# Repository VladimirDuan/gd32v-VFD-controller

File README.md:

# gd32v-VFD-controller

## The HNV-12SS62 VFD screen:

## GD32V rv32imac microcontroller:

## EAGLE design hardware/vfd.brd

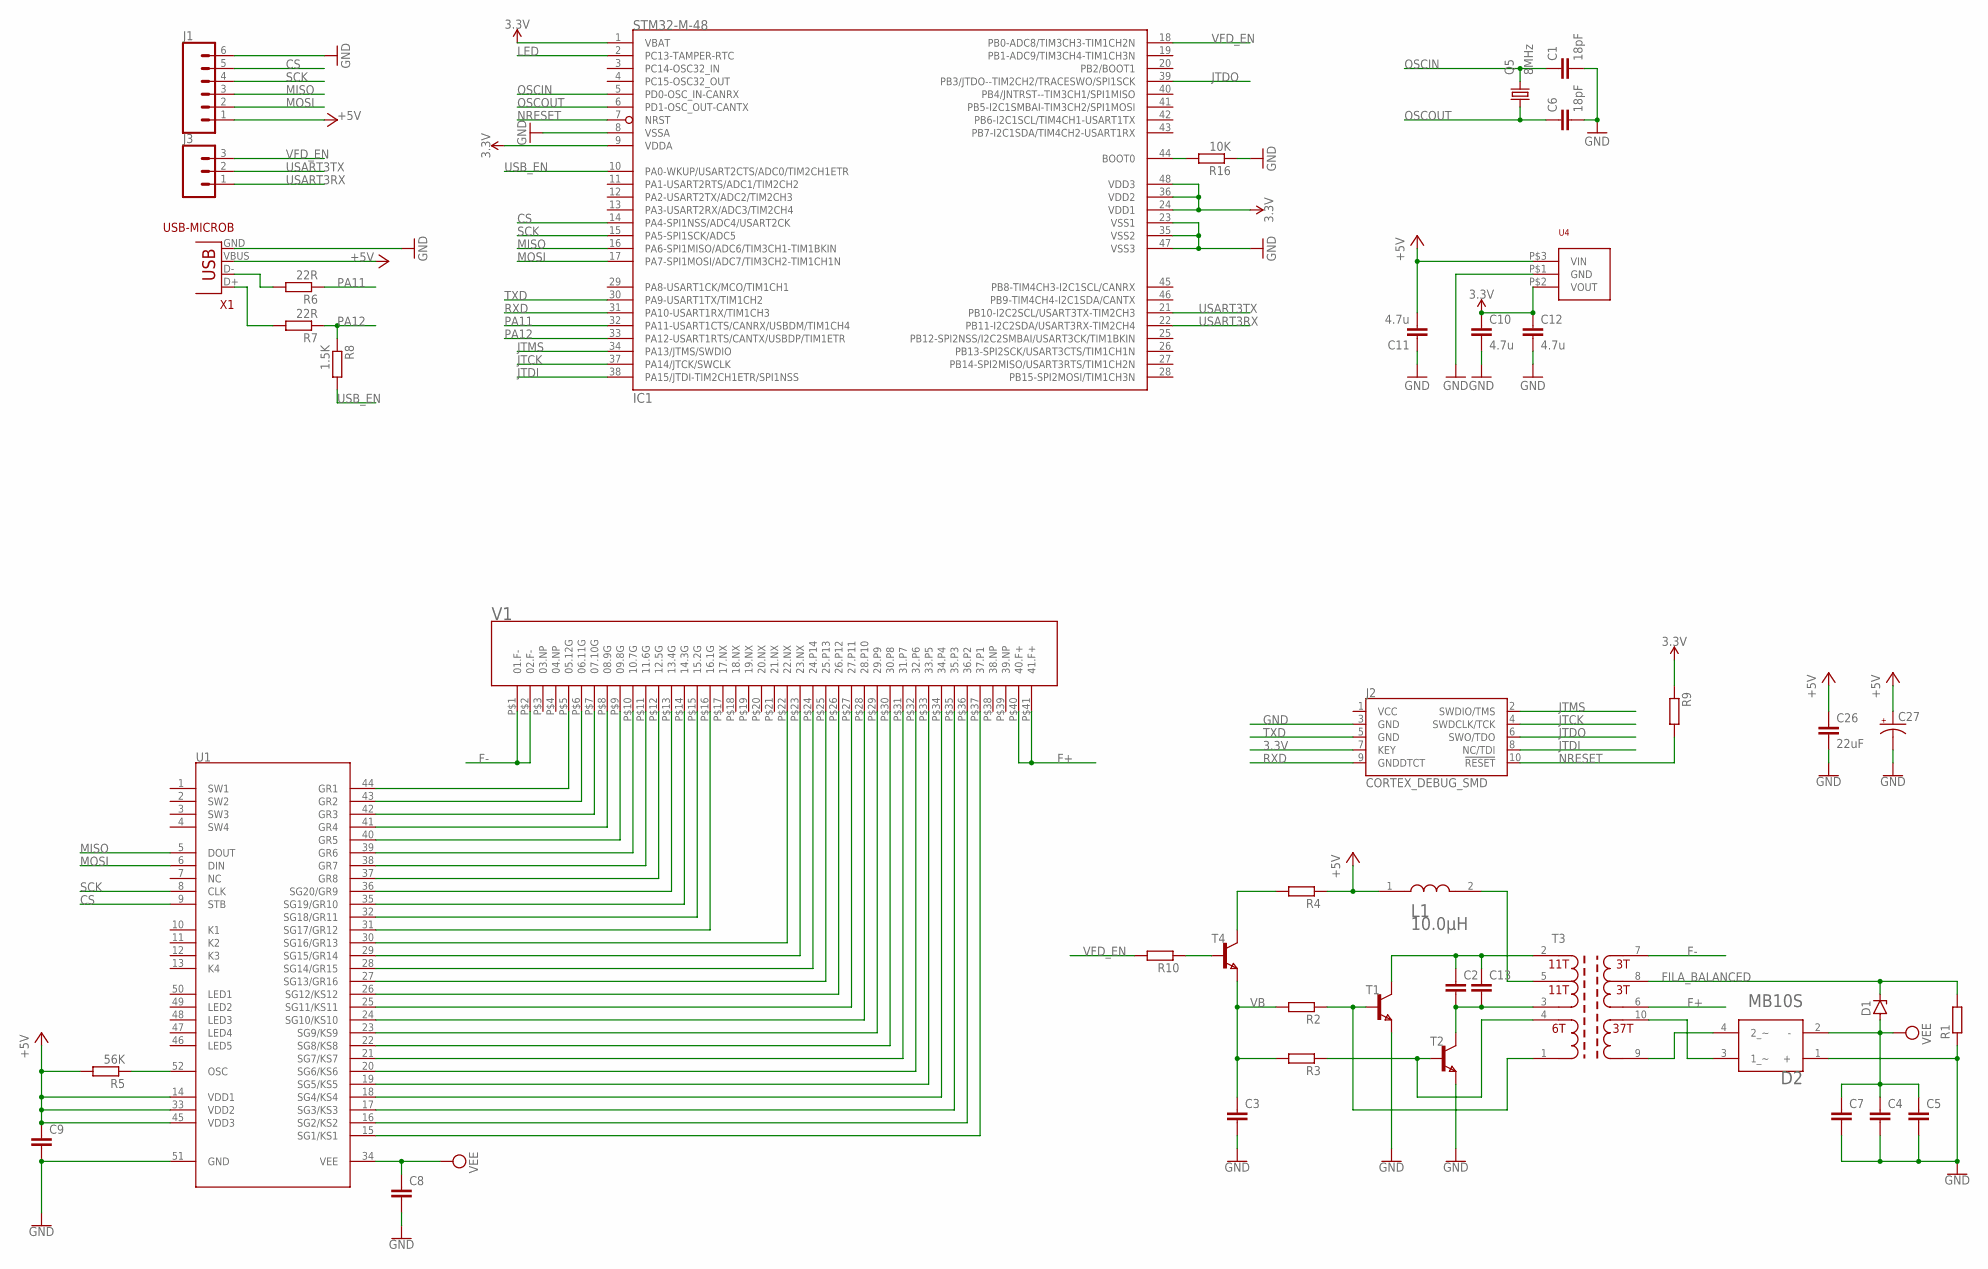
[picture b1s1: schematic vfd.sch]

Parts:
C1, C6: 18pF; C0603
C2, C13: C-EUC1206; C1206
C3, C4, C5, C7, C8, C9: C-EUC0805; C0805
C10, C11, C12: 4.7u; 0805
C26: 22uF; C1206
C27: CPOL-US153CLV-0807; 153CLV-0807
D1: ZENER-DIODESOD80C; SOD80C
D2: ON_SEMI_MB10SON_SEMI_MB10S_0_0; ON_SEMI_MB10S_0
IC1: STM32-M-48; LQFP48
J1: CONN_06NO_SILK_FEMALE_PTH; 1X06_NO_SILK
J2: CORTEX_DEBUG_SMD; SAMTECH_FTSH-105-01
J3: CONN_031X03_NO_SILK; 1X03_NO_SILK
L1: TDK_SLF7045T-100M1R3-PF; ASWPA8050
Q5: 8MHz; 3.2X2.5_KX-7
R1, R2, R3, R4, R9, R10: R-EU_R0603; R0603
R5: 56K; R0603
R6, R7: 22R; R0603
R8: 1.5K; R0603
R16: 10K; R0603
T1, T2, T4: NPNSOT23; SOT-23
T3: TRANS_VFD_ER10P5; ER10P5
U1: PT6311B; QFP52_SOT379-1
U4: MCP1703SOT-3.3V; SOT-23A
V1: VFD_12SS62; 12SS62
X1: USB-MICROB

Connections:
3.3V: C10.1, C12.1, IC1.1 (VBAT), IC1.9 (VDDA), IC1.24 (VDD1), IC1.36 (VDD2), IC1.48 (VDD3), J2.7 (KEY), R9.1, U4.P$2 (VOUT)
+5V: C9.1, C11.2, C26.1, C27.+, J1.1, L1.1, R4.1, R5.2, U1.14 (VDD1), U1.33 (VDD2), U1.45 (VDD3), U4.P$3 (VIN), X1.VBUS
CS: IC1.14 (PA4-SPI1NSS/ADC4/USART2CK), J1.5, U1.9 (STB)
F+: T3.6, V1.P$40 (40.F+), V1.P$41 (41.F+)
F-: T3.7, V1.P$1 (01.F-), V1.P$2 (02.F-)
FILA_BALANCED: D1.C, R1.2, T3.8
GND: C1.2, C3.2, C4.2, C5.2, C6.2, C7.2, C8.2, C9.2, C10.2, C11.1, C12.2, C26.2, C27.-, D2.1 (+), IC1.8 (VSSA), IC1.23 (VSS1), IC1.35 (VSS2), IC1.47 (VSS3), J1.6, J2.3 (GND), R1.1, R16.1, T1.2 (E), T2.2 (E), U1.51 (GND), U4.P$1 (GND), X1.GND
JTCK: IC1.37 (PA14/JTCK/SWCLK), J2.4 (SWDCLK/TCK)
JTDI: IC1.38 (PA15/JTDI-TIM2CH1ETR/SPI1NSS), J2.8 (NC/TDI)
JTDO: IC1.39 (PB3/JTDO--TIM2CH2/TRACESWO/SPI1SCK), J2.6 (SWO/TDO)
JTMS: IC1.34 (PA13/JTMS/SWDIO), J2.2 (SWDIO/TMS)
LED: IC1.2 (PC13-TAMPER-RTC)
MISO: IC1.16 (PA6-SPI1MISO/ADC6/TIM3CH1-TIM1BKIN), J1.3, U1.5 (DOUT)
MOSI: IC1.17 (PA7-SPI1MOSI/ADC7/TIM3CH2-TIM1CH1N), J1.2, U1.6 (DIN)
unnamed: U1.44 (GR1), V1.P$5 (05.12G)
unnamed: U1.43 (GR2), V1.P$6 (06.11G)
unnamed: U1.42 (GR3), V1.P$7 (07.10G)
unnamed: U1.41 (GR4), V1.P$8 (08.9G)
unnamed: U1.40 (GR5), V1.P$9 (09.8G)
unnamed: U1.39 (GR6), V1.P$10 (10.7G)
unnamed: U1.38 (GR7), V1.P$11 (11.6G)
unnamed: U1.37 (GR8), V1.P$12 (12.5G)
unnamed: U1.36 (SG20/GR9), V1.P$13 (13.4G)
unnamed: U1.35 (SG19/GR10), V1.P$14 (14.3G)
unnamed: U1.32 (SG18/GR11), V1.P$15 (15.2G)
unnamed: U1.31 (SG17/GR12), V1.P$16 (16.1G)
unnamed: U1.15 (SG1/KS1), V1.P$37 (37.P1)
unnamed: U1.16 (SG2/KS2), V1.P$36 (36.P2)
unnamed: U1.17 (SG3/KS3), V1.P$35 (35.P3)
unnamed: U1.18 (SG4/KS4), V1.P$34 (34.P4)
unnamed: U1.19 (SG5/KS5), V1.P$33 (33.P5)
unnamed: U1.20 (SG6/KS6), V1.P$32 (32.P6)
unnamed: U1.21 (SG7/KS7), V1.P$31 (31.P7)
unnamed: U1.22 (SG8/KS8), V1.P$30 (30.P8)
unnamed: U1.23 (SG9/KS9), V1.P$29 (29.P9)
unnamed: U1.24 (SG10/KS10), V1.P$28 (28.P10)
unnamed: U1.25 (SG11/KS11), V1.P$27 (27.P11)
unnamed: U1.26 (SG12/KS12), V1.P$26 (26.P12)
unnamed: U1.27 (SG13/GR16), V1.P$25 (25.P13)
unnamed: U1.28 (SG14/GR15), V1.P$24 (24.P14)
unnamed: U1.29 (SG15/GR14), V1.P$23 (23.NX)
unnamed: U1.30 (SG16/GR13), V1.P$22 (22.NX)
unnamed: R6.2, X1.D-
unnamed: R7.2, X1.D+
unnamed: R4.2, T4.1 (C)
unnamed: R10.1, T4.3 (B)
unnamed: R5.1, U1.52 (OSC)
unnamed: D2.4 (2_~), T3.9
unnamed: D2.3 (1_~), T3.10
unnamed: L1.2, T3.5
unnamed: C2.1, C13.1, T1.1 (C), T3.2
unnamed: C2.2, C13.2, T2.1 (C), T3.3
unnamed: R3.1, T2.3 (B), T3.4
unnamed: R2.1, T1.3 (B), T3.1
unnamed: IC1.44 (BOOT0), R16.2
NRESET: IC1.7 (NRST), J2.10 (!RESET), R9.2
OSCIN: C1.1, IC1.5 (PD0-OSC_IN-CANRX), Q5.3 (2)
OSCOUT: C6.1, IC1.6 (PD1-OSC_OUT-CANTX), Q5.1
PA11: IC1.32 (PA11-USART1CTS/CANRX/USBDM/TIM1CH4), R6.1
PA12: IC1.33 (PA12-USART1RTS/CANTX/USBDP/TIM1ETR), R7.1, R8.1
RXD: IC1.31 (PA10-USART1RX/TIM1CH3), J2.9 (GNDDTCT)
SCK: IC1.15 (PA5-SPI1SCK/ADC5), J1.4, U1.8 (CLK)
TXD: IC1.30 (PA9-USART1TX/TIM1CH2), J2.5 (GND)
USART3RX: IC1.22 (PB11-I2C2SDA/USART3RX-TIM2CH4), J3.1
USART3TX: IC1.21 (PB10-I2C2SCL/USART3TX-TIM2CH3), J3.2
USB_EN: IC1.10 (PA0-WKUP/USART2CTS/ADC0/TIM2CH1ETR), R8.2
VB: C3.1, R2.2, R3.2, T4.2 (E)
VEE: C4.1, C5.1, C7.1, C8.1, D1.A, D2.2 (-), U1.34 (VEE)
VFD_EN: IC1.18 (PB0-ADC8/TIM3CH3-TIM1CH2N), J3.3, R10.2

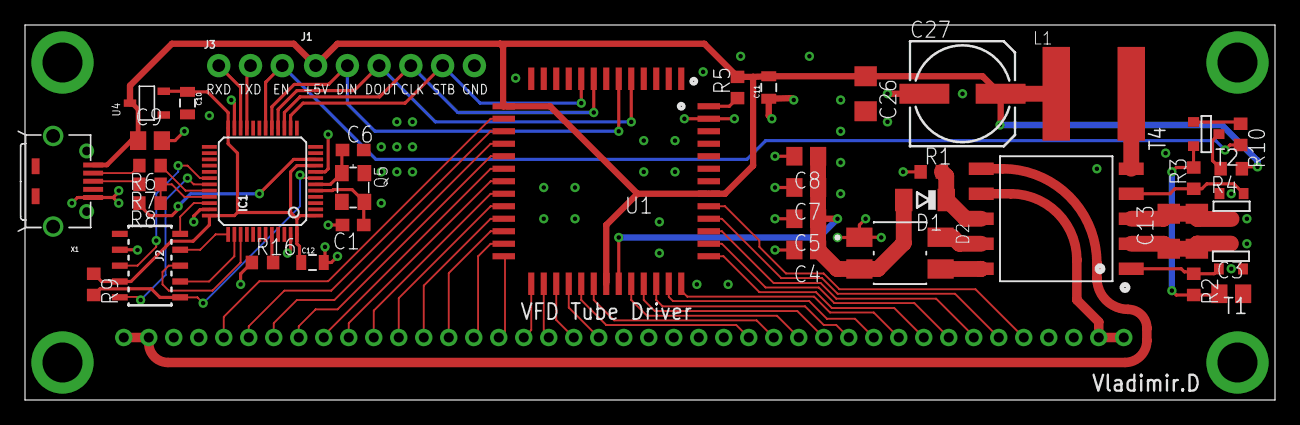
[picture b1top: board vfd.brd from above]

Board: 2 copper layers, 100.0 x 30.0 mm, 42 parts (1 on the bottom side), 68 nets.

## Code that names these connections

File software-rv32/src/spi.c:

#include "spi.h"

/*!
    \brief      configure the SPI peripheral
    \param[in]  none
    \param[out] none
    \retval     none
*/
void spi_config(void)
{
    spi_parameter_struct spi_init_struct;
    /* deinitilize SPI and the parameters */
    spi_i2s_deinit(SPI0);
    spi_struct_para_init(&spi_init_struct);

    /* configure SPI0 parameter */
    spi_init_struct.trans_mode = SPI_TRANSMODE_FULLDUPLEX;
    spi_init_struct.device_mode = SPI_MASTER;
    spi_init_struct.frame_size = SPI_FRAMESIZE_8BIT;
    spi_init_struct.clock_polarity_phase = SPI_CK_PL_HIGH_PH_2EDGE;
    spi_init_struct.nss = SPI_NSS_SOFT;
    spi_init_struct.prescale = SPI_PSC_16;
    spi_init_struct.endian = SPI_ENDIAN_LSB; // LSB First.
    spi_init(SPI0, &spi_init_struct);
}

/*!
    \brief      configure the GPIO peripheral
    \param[in]  none
    \param[out] none
    \retval     none
*/
void gpio_config(void)
{
    /* SPI0 GPIO config: SCK/PA5, MISO/PA6, MOSI/PA7 */
    gpio_init(GPIOA, GPIO_MODE_AF_PP, GPIO_OSPEED_50MHZ, GPIO_PIN_5 | GPIO_PIN_7);
    gpio_init(GPIOA, GPIO_MODE_IN_FLOATING, GPIO_OSPEED_50MHZ, GPIO_PIN_6);
    //gpio_pin_remap_config(GPIO_SPI0_REMAP, ENABLE);

    /* SPI0 GPIO config: CS/PA4 USBEN/PA0*/
    gpio_init(GPIOA, GPIO_MODE_OUT_PP, GPIO_OSPEED_50MHZ, GPIO_PIN_4 | GPIO_PIN_0);

    /* PB0/VFDEN */
    gpio_init(GPIOB, GPIO_MODE_OUT_PP, GPIO_OSPEED_50MHZ, GPIO_PIN_0);
}

/*!
    \brief      configure different peripheral clocks
    \param[in]  none
    \param[out] none
    \retval     none
*/
void rcu_config(void)
{
    rcu_periph_clock_enable(RCU_GPIOA);
    rcu_periph_clock_enable(RCU_GPIOB);
    rcu_periph_clock_enable(RCU_AF);
    rcu_periph_clock_enable(RCU_SPI0);
}

uint8_t spi_send(uint8_t data)
{
    while (RESET == spi_i2s_flag_get(SPI0, SPI_FLAG_TBE))
        ;
    spi_i2s_data_transmit(SPI0, data);
    return 0; //TODO: should return duplex receive value.
}

uint8_t stb_high(void)
{
    delay_1us(10);
    GPIO_BOP(GPIOA) = GPIO_PIN_4;
    delay_1us(10);
}

uint8_t stb_low(void)
{
    delay_1us(10);
    GPIO_BC(GPIOA) = GPIO_PIN_4;
    delay_1us(10);
}

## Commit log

2019-10-08 Add design files.
2019-10-08 Add some display patterns.
2019-10-09 add usb-hid.
2019-10-10 Add some photos.
2019-10-10 readme update.

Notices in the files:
parts and their libraries:
crystal-geyer_V1_0: Copyright: Geyer-Electronic
SparkFun-Connectors: Licensing: Creative Commons ShareAlike 4.0 International - https://creativecommons.org/licenses/by-sa/4.0
